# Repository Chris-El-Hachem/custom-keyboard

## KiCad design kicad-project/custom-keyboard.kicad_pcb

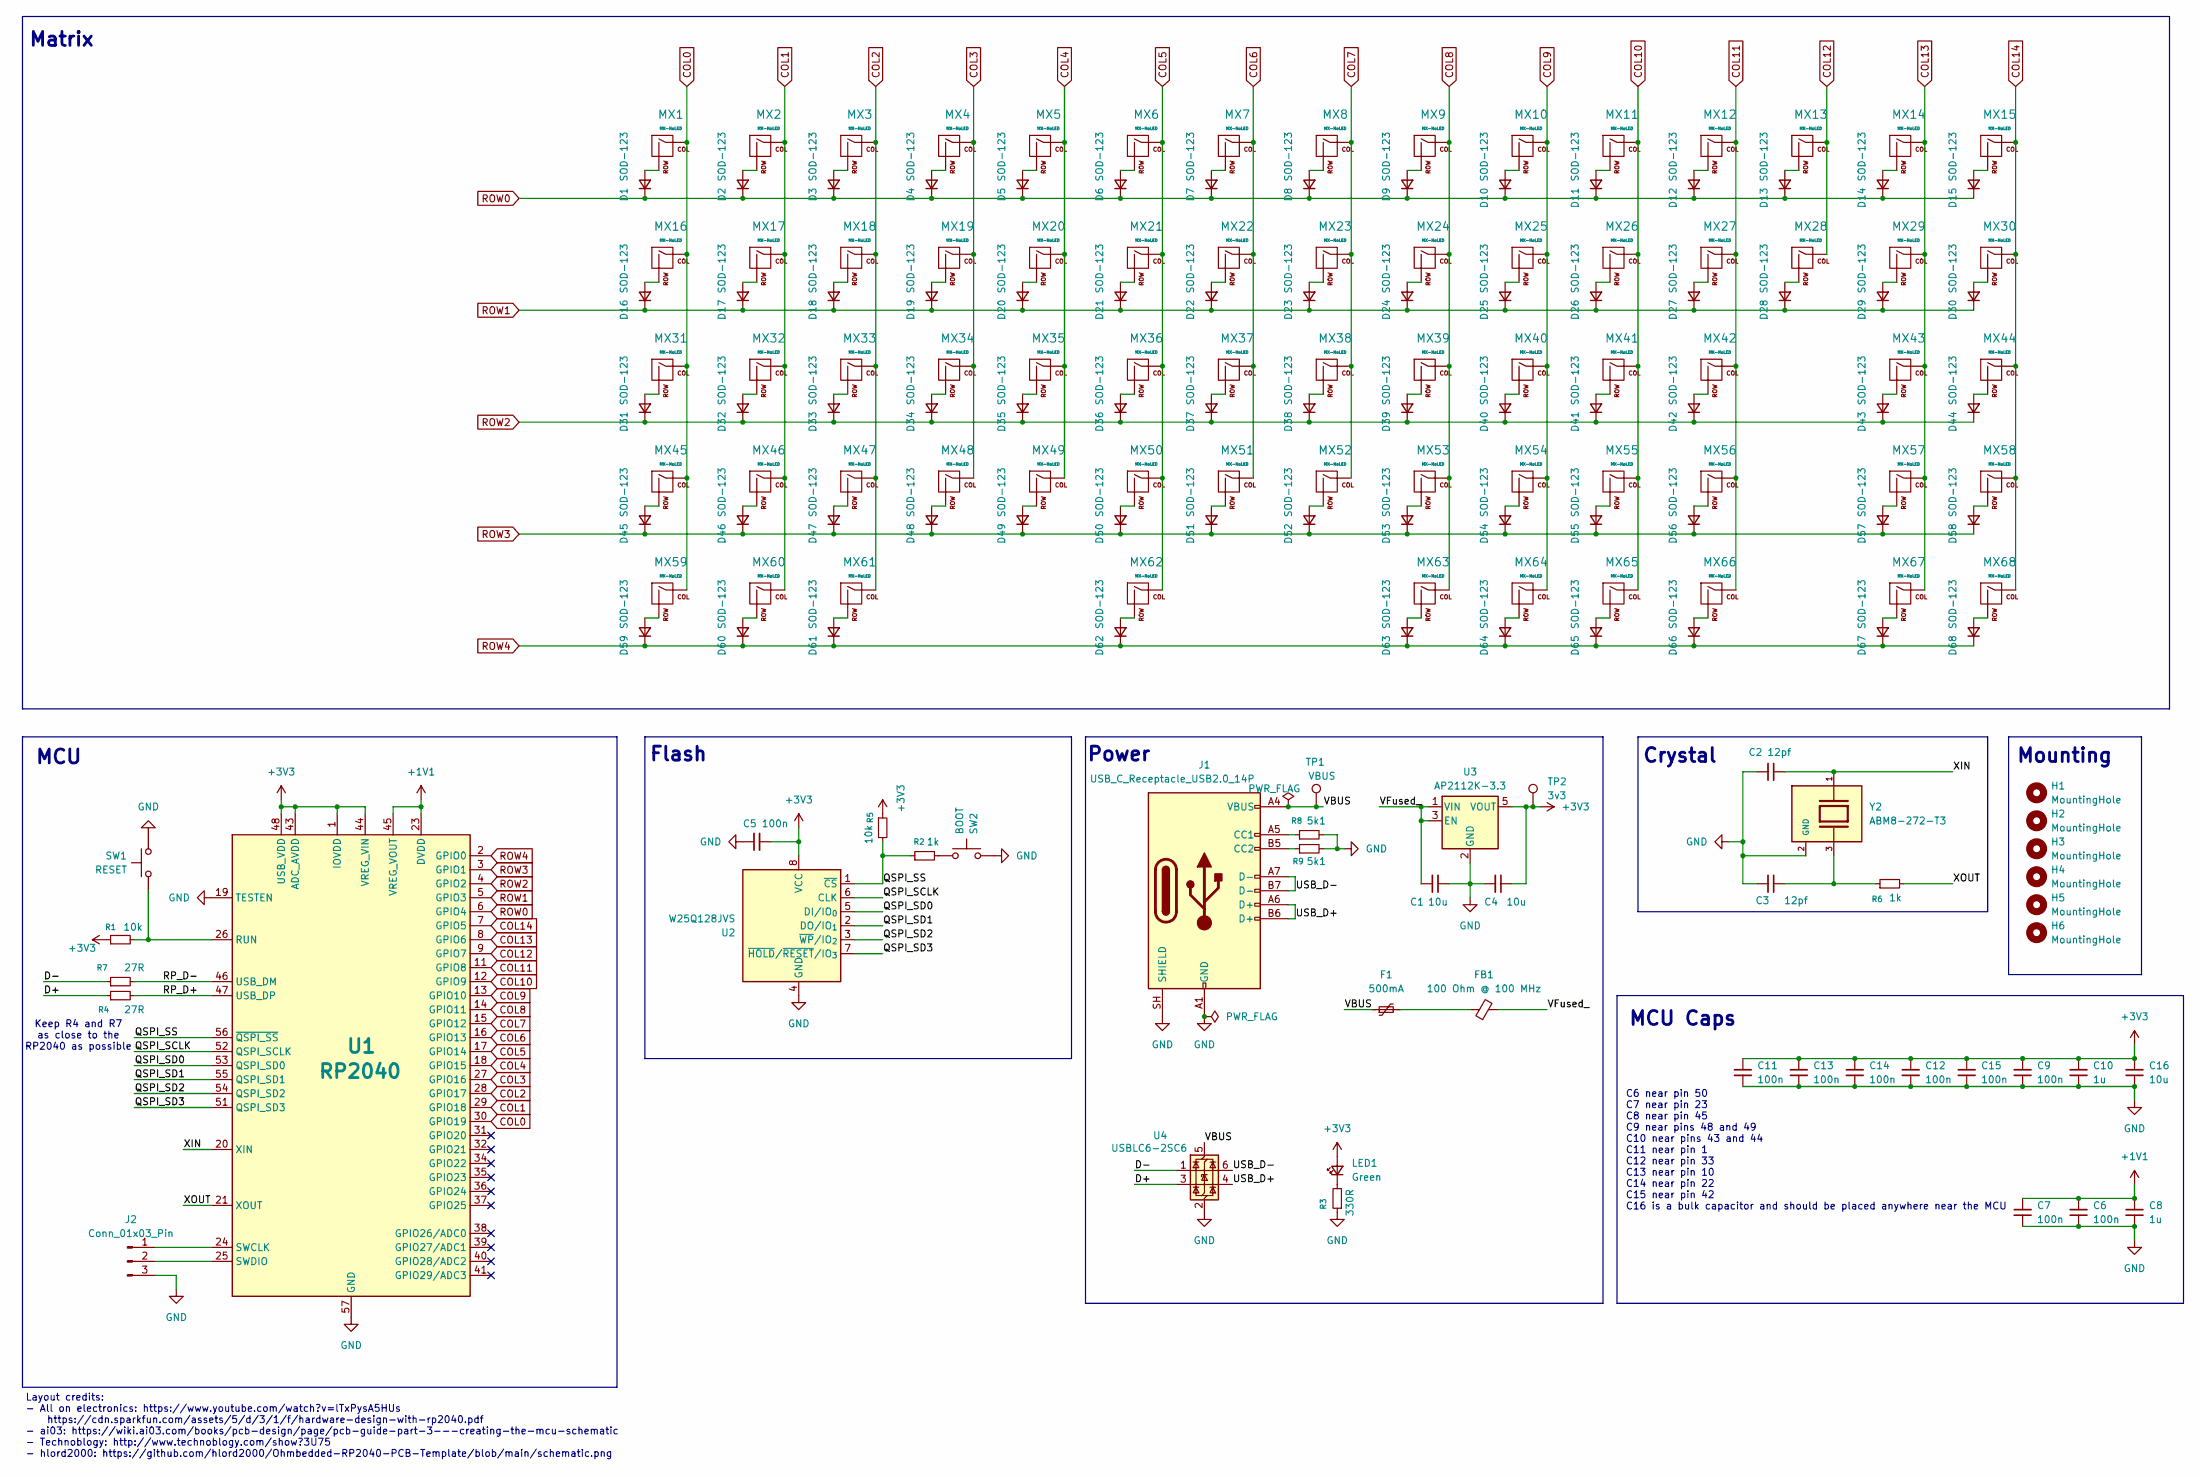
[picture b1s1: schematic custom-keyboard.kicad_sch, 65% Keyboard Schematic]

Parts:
C1, C4, C16: 10u; C_0805_2012Metric
C2, C3: 12pf; C_0805_2012Metric
C5, C6, C7, C9, C11, C12, C13, C14, C15: 100n; C_0805_2012Metric
C8, C10: 1u; C_0805_2012Metric
D1, D2, D3, D4, D5, D6, D7, D8, D9, D10, D11, D12, D13, D14, D15, D16, D17, D18, D19, D20, D21, D22, D23, D24, D25, D26, D27, D28, D29, D30, D31, D32, D33, D34, D35, D36, D37, D38, D39, D40, D41, D42, D43, D44, D45, D46, D47, D48, D49, D50, D51, D52, D53, D54, D55, D56, D57, D58, D59, D60, D61, D62, D63, D64, D65, D66, D67, D68: SOD-123; D_SOD-123
F1: 500mA; Fuse_1206_3216Metric_Pad1.42x1.75mm_HandSolder
FB1: 100 Ohm @ 100 MHz; L_0805_2012Metric
H1, H2, H3, H4, H5, H6: MountingHole; MountingHole_3.2mm_M3
J1: USB_C_Receptacle_USB2.0_14P; USB_C_Receptacle_HCTL_HC-TYPE-C-16P-01A
J2: Conn_01x03_Pin; PinHeader_1x03_P1.00mm_Vertical
LED1: Green; LED_0805_2012Metric
MX1, MX2, MX3, MX4, MX5, MX6, MX7, MX8, MX9, MX10, MX11, MX12, MX13, MX15, MX17, MX18, MX19, MX20, MX21, MX22, MX23, MX24, MX25, MX26, MX27, MX28, MX30, MX32, MX33, MX34, MX35, MX36, MX37, MX38, MX39, MX40, MX41, MX42, MX44, MX46, MX47, MX48, MX49, MX50, MX51, MX52, MX53, MX54, MX55, MX57, MX58, MX63, MX64, MX65, MX66, MX67, MX68: MX-NoLED; MX-Hotswap-1U
MX14: MX-NoLED; MX-Hotswap-2U
MX16, MX29: MX-NoLED; MX-Hotswap-1.5U
MX31, MX56: MX-NoLED; MX-Hotswap-1.75U
MX43, MX45: MX-NoLED; MX-Hotswap-2.25U
MX59, MX60, MX61: MX-NoLED; MX-Hotswap-1.25U
MX62: MX-NoLED; MX-Hotswap-6.25U
R1, R5: 10k; R_0805_2012Metric
R2, R6: 1k; R_0805_2012Metric
R3: 330R; R_0805_2012Metric
R4, R7: 27R; R_0402_1005Metric
R8, R9: 5k1; R_0805_2012Metric
SW1: RESET; SKQG-1155865
SW2: BOOT; SKQG-1155865
TP1: VBUS; TestPoint_Loop_D2.50mm_Drill1.0mm
TP2: 3v3; TestPoint_Loop_D2.50mm_Drill1.0mm
U1: RP2040; QFN-56-1EP_7x7mm_P0.4mm_EP3.2x3.2mm
U2: W25Q128JVS; SOIC-8_5.3x5.3mm_P1.27mm
U3: AP2112K-3.3; SOT-23-5
U4: USBLC6-2SC6; SOT-23-6
Y2: ABM8-272-T3; XTAL_ABM8-272-T3; MPN ABM8-272-T3

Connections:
+1V1: C6.1, C7.1, C8.1, U1.23 (DVDD), U1.45 (VREG_VOUT), U1.50 (DVDD)
+3V3: C4.2, C5.2, C9.1, C10.1, C11.1, C12.1, C13.1, C14.1, C15.1, C16.1, LED1.2 (A), R1.1, R5.1, TP2.1 (1_1), U1.1 (IOVDD), U1.10 (IOVDD), U1.22 (IOVDD), U1.33 (IOVDD), U1.42 (IOVDD), U1.43 (ADC_AVDD), U1.44 (VREG_VIN), U1.48 (USB_VDD), U1.49 (IOVDD), U2.8 (VCC), U3.5 (VOUT)
/D+: R4.1, U4.3 (I/O2)
/D-: R7.1, U4.1 (I/O1)
/QSPI_SCLK: U1.52 (QSPI_SCLK), U2.6 (CLK)
/QSPI_SD0: U1.53 (QSPI_SD0), U2.5 (DI/IO_{0})
/QSPI_SD1: U1.55 (QSPI_SD1), U2.2 (DO/IO_{1})
/QSPI_SD2: U1.54 (QSPI_SD2), U2.3 (~WP/IO_{2})
/QSPI_SD3: U1.51 (QSPI_SD3), U2.7 (~HOLD/~RESET/IO_{3})
/QSPI_SS: R2.1, R5.2, U1.56 (~QSPI_SS), U2.1 (~CS)
/RP_D+: R4.2, U1.47 (USB_DP)
/RP_D-: R7.2, U1.46 (USB_DM)
/USB_D+: J1.A6 (D+), J1.B6 (D+), U4.4 (I/O2)
/USB_D-: J1.A7 (D-), J1.B7 (D-), U4.6 (I/O1)
/VBUS: F1.1, J1.A4 (VBUS), J1.A9 (VBUS), J1.B4 (VBUS), J1.B9 (VBUS), TP1.1 (1_1), U4.5 (VBUS)
/VFused_: C1.1, FB1.2, U3.1 (VIN), U3.3 (EN)
/XIN: C2.2, U1.20 (XIN), Y2.1
/XOUT: R6.2, U1.21 (XOUT)
COL0: MX1.1 (COL), MX16.1 (COL), MX31.1 (COL), MX45.1 (COL), MX59.1 (COL), U1.30 (GPIO19)
COL1: MX2.1 (COL), MX17.1 (COL), MX32.1 (COL), MX46.1 (COL), MX60.1 (COL), U1.29 (GPIO18)
COL2: MX3.1 (COL), MX18.1 (COL), MX33.1 (COL), MX47.1 (COL), MX61.1 (COL), U1.28 (GPIO17)
COL3: MX4.1 (COL), MX19.1 (COL), MX34.1 (COL), MX48.1 (COL), U1.27 (GPIO16)
COL4: MX5.1 (COL), MX20.1 (COL), MX35.1 (COL), MX49.1 (COL), U1.18 (GPIO15)
COL5: MX6.1 (COL), MX21.1 (COL), MX36.1 (COL), MX50.1 (COL), MX62.1 (COL), U1.17 (GPIO14)
COL6: MX7.1 (COL), MX22.1 (COL), MX37.1 (COL), MX51.1 (COL), U1.16 (GPIO13)
COL7: MX8.1 (COL), MX23.1 (COL), MX38.1 (COL), MX52.1 (COL), U1.15 (GPIO12)
COL8: MX9.1 (COL), MX24.1 (COL), MX39.1 (COL), MX53.1 (COL), MX63.1 (COL), U1.14 (GPIO11)
COL9: MX10.1 (COL), MX25.1 (COL), MX40.1 (COL), MX54.1 (COL), MX64.1 (COL), U1.13 (GPIO10)
COL10: MX11.1 (COL), MX26.1 (COL), MX41.1 (COL), MX55.1 (COL), MX65.1 (COL), U1.12 (GPIO9)
COL11: MX12.1 (COL), MX27.1 (COL), MX42.1 (COL), MX56.1 (COL), MX66.1 (COL), U1.11 (GPIO8)
COL12: MX13.1 (COL), MX28.1 (COL), U1.9 (GPIO7)
COL13: MX14.1 (COL), MX29.1 (COL), MX43.1 (COL), MX57.1 (COL), MX67.1 (COL), U1.8 (GPIO6)
COL14: MX15.1 (COL), MX30.1 (COL), MX44.1 (COL), MX58.1 (COL), MX68.1 (COL), U1.7 (GPIO5)
GND: C1.2, C2.1, C3.1, C4.1, C5.1, C6.2, C7.2, C8.2, C9.2, C10.2, C11.2, C12.2, C13.2, C14.2, C15.2, C16.2, J1.A1 (GND), J1.A12 (GND), J1.B1 (GND), J1.B12 (GND), J1.SH (SHIELD), J2.3, R3.1, R8.2, R9.2, SW1.1, SW2.1, U1.19 (TESTEN), U1.57 (GND), U2.4 (GND), U3.2 (GND), U4.2 (GND), Y2.2 (GND), Y2.4 (GND)
unnamed: C3.2, R6.1, Y2.3
unnamed: D1.2 (A), MX1.2 (ROW)
unnamed: D2.2 (A), MX2.2 (ROW)
unnamed: D3.2 (A), MX3.2 (ROW)
unnamed: D4.2 (A), MX4.2 (ROW)
unnamed: D5.2 (A), MX5.2 (ROW)
unnamed: D6.2 (A), MX6.2 (ROW)
unnamed: D7.2 (A), MX7.2 (ROW)
unnamed: D8.2 (A), MX8.2 (ROW)
unnamed: D9.2 (A), MX9.2 (ROW)
unnamed: D10.2 (A), MX10.2 (ROW)
unnamed: D11.2 (A), MX11.2 (ROW)
unnamed: D12.2 (A), MX12.2 (ROW)
unnamed: D13.2 (A), MX13.2 (ROW)
unnamed: D14.2 (A), MX14.2 (ROW)
unnamed: D15.2 (A), MX15.2 (ROW)
unnamed: D16.2 (A), MX16.2 (ROW)
unnamed: D17.2 (A), MX17.2 (ROW)
unnamed: D18.2 (A), MX18.2 (ROW)
unnamed: D19.2 (A), MX19.2 (ROW)
unnamed: D20.2 (A), MX20.2 (ROW)
unnamed: D21.2 (A), MX21.2 (ROW)
unnamed: D22.2 (A), MX22.2 (ROW)
unnamed: D23.2 (A), MX23.2 (ROW)
unnamed: D24.2 (A), MX24.2 (ROW)
unnamed: D25.2 (A), MX25.2 (ROW)
unnamed: D26.2 (A), MX26.2 (ROW)
unnamed: D27.2 (A), MX27.2 (ROW)
unnamed: D28.2 (A), MX28.2 (ROW)
unnamed: D29.2 (A), MX29.2 (ROW)
unnamed: D30.2 (A), MX30.2 (ROW)
unnamed: D31.2 (A), MX31.2 (ROW)
unnamed: D32.2 (A), MX32.2 (ROW)
unnamed: D33.2 (A), MX33.2 (ROW)
unnamed: D34.2 (A), MX34.2 (ROW)
unnamed: D35.2 (A), MX35.2 (ROW)
unnamed: D36.2 (A), MX36.2 (ROW)
unnamed: D37.2 (A), MX37.2 (ROW)
unnamed: D38.2 (A), MX38.2 (ROW)
unnamed: D39.2 (A), MX39.2 (ROW)
unnamed: D40.2 (A), MX40.2 (ROW)
unnamed: D41.2 (A), MX41.2 (ROW)
unnamed: D42.2 (A), MX42.2 (ROW)
unnamed: D43.2 (A), MX43.2 (ROW)
unnamed: D44.2 (A), MX44.2 (ROW)
unnamed: D45.2 (A), MX45.2 (ROW)
unnamed: D46.2 (A), MX46.2 (ROW)
unnamed: D47.2 (A), MX47.2 (ROW)
unnamed: D48.2 (A), MX48.2 (ROW)
unnamed: D49.2 (A), MX49.2 (ROW)
unnamed: D50.2 (A), MX50.2 (ROW)
unnamed: D51.2 (A), MX51.2 (ROW)
unnamed: D52.2 (A), MX52.2 (ROW)
unnamed: D53.2 (A), MX53.2 (ROW)
unnamed: D54.2 (A), MX54.2 (ROW)
unnamed: D55.2 (A), MX55.2 (ROW)
unnamed: D56.2 (A), MX56.2 (ROW)
unnamed: D57.2 (A), MX57.2 (ROW)
unnamed: D58.2 (A), MX58.2 (ROW)
unnamed: D59.2 (A), MX59.2 (ROW)
unnamed: D60.2 (A), MX60.2 (ROW)
unnamed: D61.2 (A), MX61.2 (ROW)
unnamed: D62.2 (A), MX62.2 (ROW)
unnamed: D63.2 (A), MX63.2 (ROW)
unnamed: D64.2 (A), MX64.2 (ROW)
unnamed: D65.2 (A), MX65.2 (ROW)
unnamed: D66.2 (A), MX66.2 (ROW)
unnamed: D67.2 (A), MX67.2 (ROW)
unnamed: D68.2 (A), MX68.2 (ROW)
unnamed: F1.2, FB1.1
unnamed: J1.A5 (CC1), R8.1
unnamed: J1.B5 (CC2), R9.1
unnamed: J2.1, U1.24 (SWCLK)
unnamed: J2.2, U1.25 (SWDIO)
unnamed: LED1.1 (K), R3.2
unnamed: R2.2, SW2.2
unnamed: R1.2, SW1.2, U1.26 (RUN)
ROW0: D1.1 (K), D2.1 (K), D3.1 (K), D4.1 (K), D5.1 (K), D6.1 (K), D7.1 (K), D8.1 (K), D9.1 (K), D10.1 (K), D11.1 (K), D12.1 (K), D13.1 (K), D14.1 (K), D15.1 (K), U1.6 (GPIO4)
ROW1: D16.1 (K), D17.1 (K), D18.1 (K), D19.1 (K), D20.1 (K), D21.1 (K), D22.1 (K), D23.1 (K), D24.1 (K), D25.1 (K), D26.1 (K), D27.1 (K), D28.1 (K), D29.1 (K), D30.1 (K), U1.5 (GPIO3)
ROW2: D31.1 (K), D32.1 (K), D33.1 (K), D34.1 (K), D35.1 (K), D36.1 (K), D37.1 (K), D38.1 (K), D39.1 (K), D40.1 (K), D41.1 (K), D42.1 (K), D43.1 (K), D44.1 (K), U1.4 (GPIO2)
ROW3: D45.1 (K), D46.1 (K), D47.1 (K), D48.1 (K), D49.1 (K), D50.1 (K), D51.1 (K), D52.1 (K), D53.1 (K), D54.1 (K), D55.1 (K), D56.1 (K), D57.1 (K), D58.1 (K), U1.3 (GPIO1)
ROW4: D59.1 (K), D60.1 (K), D61.1 (K), D62.1 (K), D63.1 (K), D64.1 (K), D65.1 (K), D66.1 (K), D67.1 (K), D68.1 (K), U1.2 (GPIO0)

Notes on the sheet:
Layout credits: - All on electronics: https://www.youtube.com/watch?v=lTxPysA5HUs https://cdn.sparkfun.com/assets/5/d/3/1/f/hardware-design-with-rp2040.pdf - ai03: https://wiki.ai03.com/books/pcb-design/page/pcb-guide-part-3---creating-the-mcu-schematic - Technoblogy: http://www.technoblogy.com/sho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
Power
Flash
MCU Caps
Keep R4 and R7 as close to the RP2040 as possible
Matrix
MCU
Crystal
C6 near pin 50 C7 near pin 23 C8 near pin 45 C9 near pins 48 and 49 C10 near pins 43 and 44 C11 near pin 1 C12 near pin 33 C13 near pin 10 C14 near pin 22 C15 near pin 42 C16 is a bulk capacitor and should be placed anywhere near the MCU
Mounting

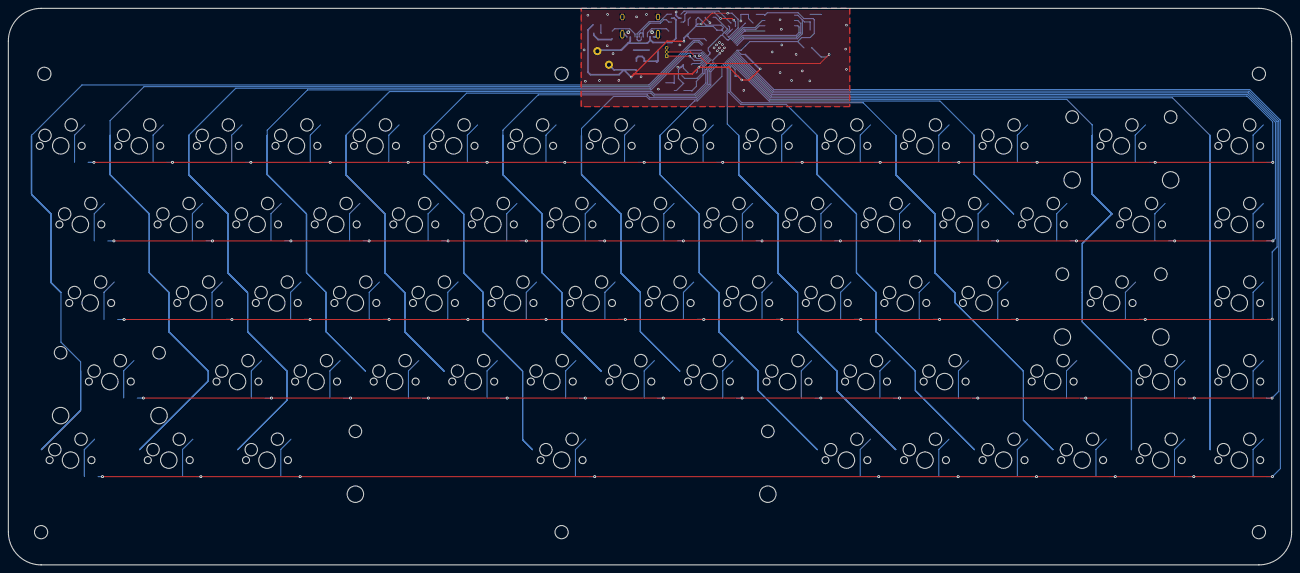
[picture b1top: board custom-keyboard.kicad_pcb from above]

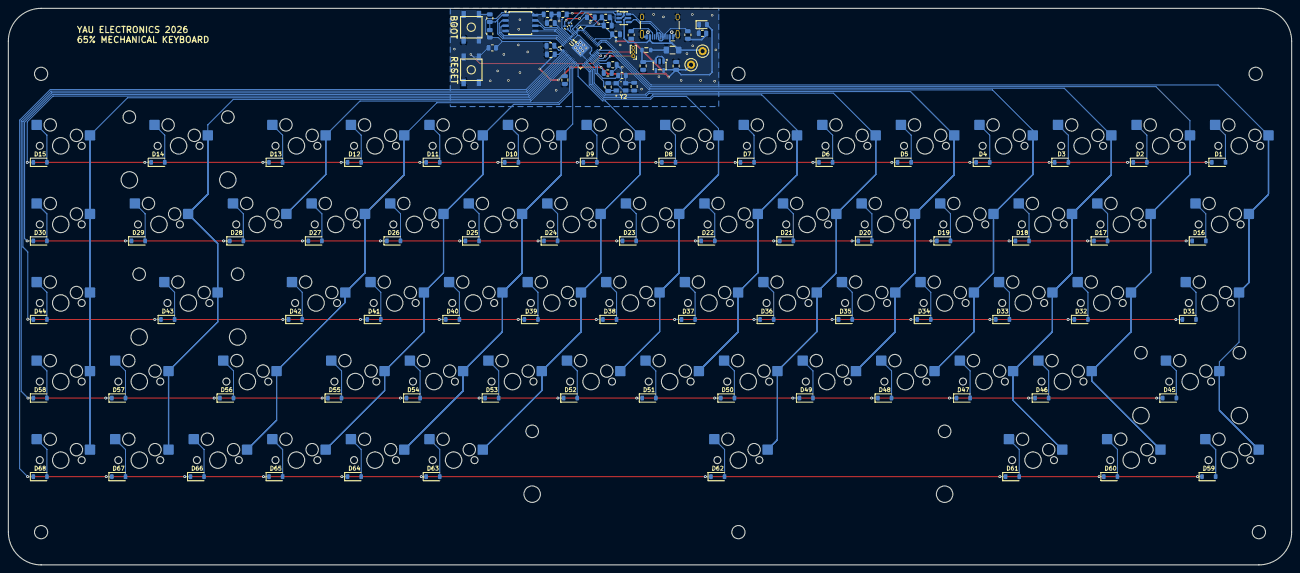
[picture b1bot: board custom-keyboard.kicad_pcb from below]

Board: 2 copper layers, 311.2 x 134.9 mm, 181 parts (175 on the bottom side), 116 nets.
